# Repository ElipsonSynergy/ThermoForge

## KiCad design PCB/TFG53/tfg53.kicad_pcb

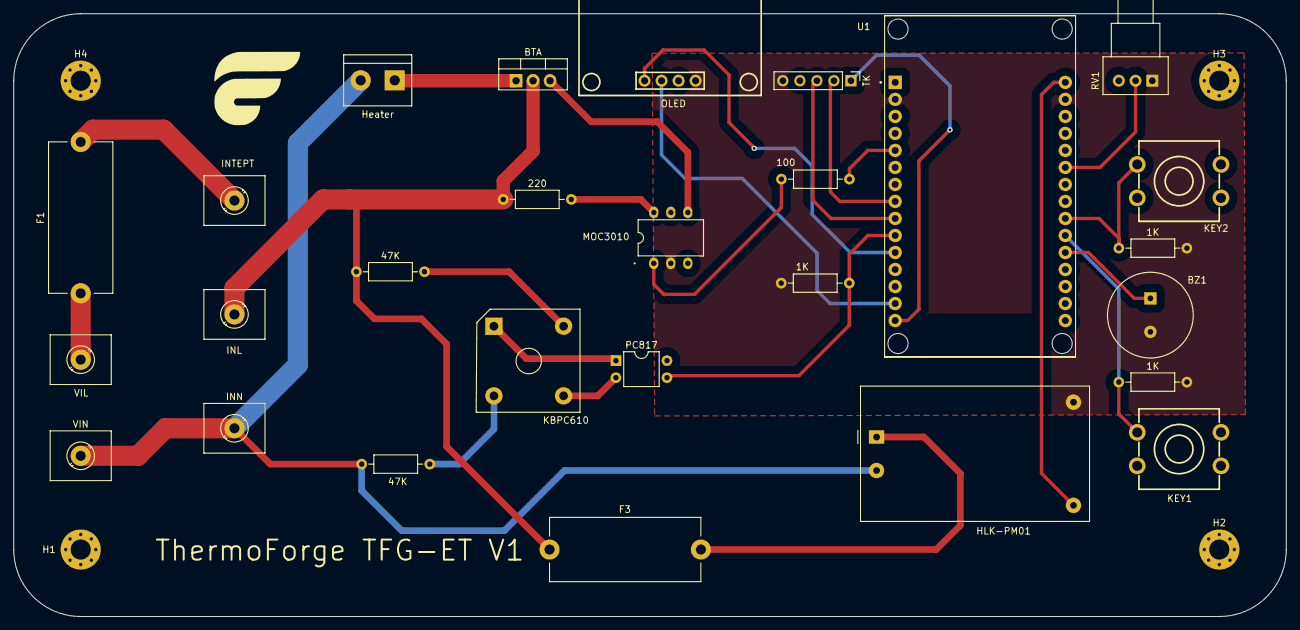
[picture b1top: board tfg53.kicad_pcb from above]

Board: 2 copper layers, 190.0 x 90.0 mm, 31 parts (0 on the bottom side), 27 nets.

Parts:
1K, 1K#2, 1K#3: 1K; R_Axial_DIN0207_L6.3mm_D2.5mm_P10.16mm_Horizontal
47K, 47K#2: 47K; R_Axial_DIN0207_L6.3mm_D2.5mm_P10.16mm_Horizontal
100: 100; R_Axial_DIN0207_L6.3mm_D2.5mm_P10.16mm_Horizontal
220: 220; R_Axial_DIN0207_L6.3mm_D2.5mm_P10.16mm_Horizontal
BTA: BTA16-600B; TO-220-3_Vertical
BZ1: PS1240P02BT; Piezo_Transducer_THT_PS1240P02BT
F1: 16A; Fuseholder_Cylinder-5x20mm_Stelvio-Kontek_PTF78_Horizontal_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
F3: 1A; Fuseholder_Cylinder-5x20mm_Stelvio-Kontek_PTF78_Horizontal_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
H1, H2, H3, H4: MH; MountingHole_3mm_Pad_Via
HLK-PM01: HLK-PM01; Converter_ACDC_HiLink_HLK-PMxx
Heater: Heater; TerminalBlock_bornier-2_P5.08mm
INL: Iout; TerminalBlock_MetzConnect_360271_1x01_Horizontal_ScrewM3.0_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
INN: IN; TerminalBlock_MetzConnect_360271_1x01_Horizontal_ScrewM3.0_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
INTEPT: Iin; TerminalBlock_MetzConnect_360271_1x01_Horizontal_ScrewM3.0_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
KBPC610: VS-KBPC610; Diode_Bridge_Vishay_KBPC6
KEY1: menu; KEY-TH_4P-L12.0-W12.0-P5.00-LS13.4
KEY2: select; KEY-TH_4P-L12.0-W12.0-P5.00-LS13.4
MOC3010: MOC3010; DIP-6_L9.6-W6.4-P2.54-LS7.6-BL
OLED: HS96L03W2C03; OLED-TH_L27.8-W27.2-P2.54_C9900033791
PC817: PC817; DIP-4_W7.62mm
RV1: 5K; Potentiometer_Alps_RK09Y11_Single_Horizontal
TK: Thermocuple; PinHeader_1x05_P2.54mm_Vertical
U1: ESP32-DEVKIT-V1; MODULE_ESP32_DEVKIT_V1
VIL: L; TerminalBlock_MetzConnect_360271_1x01_Horizontal_ScrewM3.0_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
VIN: N; TerminalBlock_MetzConnect_360271_1x01_Horizontal_ScrewM3.0_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

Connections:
3v3: KEY1.4, KEY2.4, OLED.2 (VCC), PC817.4, RV1.3, TK.4, U1.1 (3V3)
+5V: HLK-PM01.4 (+Vout), U1.30 (VIN)
CS: TK.2, U1.8 (D5)
GND: 1K.1, 1K#2.2, 1K#3.2, BZ1.2, HLK-PM01.3 (-Vout), MOC3010.2, OLED.1 (GND), RV1.1, TK.5, U1.2 (GND), U1.29 (GND)
GPIO 4: 100.2, U1.5 (D4)
GPIO 19: 1K.2, PC817.3, U1.10 (D19)
GPIO 27: RV1.2, U1.25 (D27)
GPIO 32: 1K#3.1, KEY1.2, U1.21 (D32)
GPIO 33: 1K#2.1, KEY2.2, U1.22 (D33)
L: 47K.1, 220.1, BTA.2 (A2), F3.1, INL.1
N: 47K#2.2, HLK-PM01.2 (AC/N), Heater.2, INN.1, VIN.1
unnamed: KBPC610.1 (+), PC817.1
unnamed: KBPC610.3 (-), PC817.2
unnamed: 47K#2.1, KBPC610.2
unnamed: 47K.2, KBPC610.4
unnamed: F1.1, VIL.1
unnamed: F1.2, INTEPT.1
unnamed: F3.2, HLK-PM01.1 (AC/L)
unnamed: BTA.1 (A1), Heater.1
unnamed: BTA.3 (G), MOC3010.4
unnamed: 220.2, MOC3010.6
unnamed: 100.1, MOC3010.1
SCK: TK.3, U1.9 (D18)
SDA: OLED.4 (SDA), U1.11 (D21)
SLC: OLED.3 (SCL), U1.14 (D22)
SO: TK.1, U1.15 (D23)
SOUND: BZ1.1, U1.20 (D35)

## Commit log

2024-11-11 Power supply & Interface PCB
2024-11-12 Optoacoplador MOC3010 added
2024-11-18 Termocuple code
2024-11-26 Placa terminada
2024-11-26 Gerber files
2024-11-30 PCB view
2024-11-30 Interfa UI
2024-11-30 PID declarado
2024-12-01 First deadline
2024-12-01 Deadline I
2024-12-09 Some backups
